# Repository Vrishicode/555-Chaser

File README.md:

# 555-Chaser
Basic description: This is a blinky board/ 555 led chaser which i made for forge in hack club and i changed it and made it so that it looks like a clock.
Why i built it: So i was looking for a project in the guides that was not too difficult so that i could get my hands dirty/ get used to how kicad works and building by first pcb. I just wanted to build this so i would understand how kicad works before moving onto harder/more complex projects and make things that are interesting and make things to build a portfolio.

Whats next: I used this to understand the basics of kicad before moving onto a harder guide/project which is the flight controller and after i will move on to making various controllers for video games like for a racing game, war thunder, etc.

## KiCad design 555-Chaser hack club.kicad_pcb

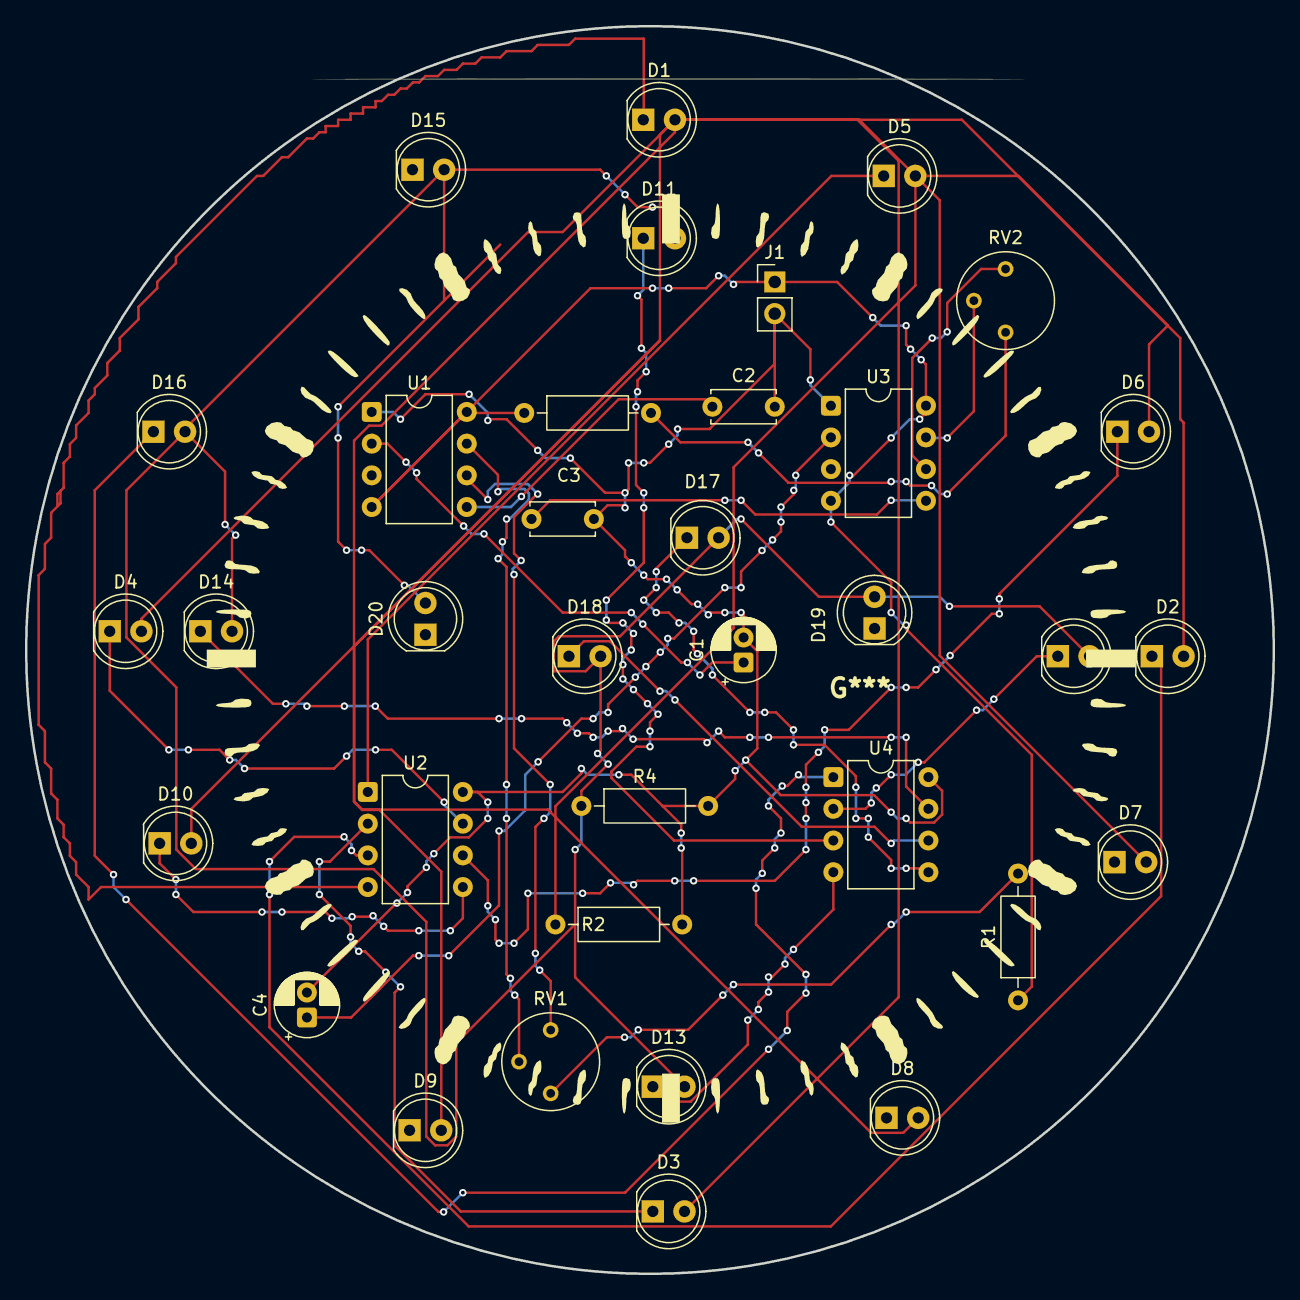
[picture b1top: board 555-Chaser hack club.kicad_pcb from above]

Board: 2 copper layers, 100.0 x 100.0 mm, 35 parts (0 on the bottom side), 28 nets.

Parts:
C1, C4: 1 uF; CP_Radial_D5.0mm_P2.00mm
C2, C3: 0.01 uF; C_Disc_D5.0mm_W2.5mm_P5.00mm
D1, D2, D3, D4, D5, D6, D7, D8, D9, D10, D11, D12, D13, D14, D15, D16, D17, D18, D19, D20: LED; LED_D5.0mm
J1: Conn_01x02_Socket; PinHeader_1x02_P2.54mm_Vertical
R1, R3: 1k; R_Axial_DIN0207_L6.3mm_D2.5mm_P10.16mm_Horizontal
R2, R4: 470; R_Axial_DIN0207_L6.3mm_D2.5mm_P10.16mm_Horizontal
RV1, RV2: 50k; Potentiometer_Bourns_3339P_Vertical
U1, U3: NE555P; DIP-8_W7.62mm
U2, U4: 4017; DIP-8_W7.62mm

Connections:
+5V: J1.1, R1.1, R3.1, U1.4 (~RST), U1.8 (VCC), U3.4 (~RST), U3.8 (VCC)
GND: C1.2, C2.2, C3.2, C4.2, J1.2, R2.2, R4.2, U1.1 (GND), U2.8 (VSS), U3.1 (GND), U4.8 (VSS)
unnamed: D1.2 (A), D2.2 (A), D3.2 (A), D4.2 (A), D5.2 (A), D6.2 (A), D7.2 (A), D8.2 (A), D9.2 (A), D10.2 (A), R2.1
unnamed: D1.1 (K), U2.4 (Q2)
unnamed: D2.1 (K), U2.3 (Q0)
unnamed: D3.1 (K), U2.2 (Q1)
unnamed: D4.1 (K), U2.7 (Q3)
unnamed: D5.1 (K), U2.1 (Q5)
unnamed: D6.1 (K), U2.6 (Q7)
unnamed: D10.1 (K), U2.5 (Q6)
unnamed: D11.2 (A), D12.2 (A), D13.2 (A), D14.2 (A), D15.2 (A), D16.2 (A), D17.2 (A), D18.2 (A), D19.2 (A), D20.2 (A), R4.1
unnamed: D11.1 (K), U4.3 (Q0)
unnamed: D12.1 (K), U4.2 (Q1)
unnamed: D13.1 (K), U4.4 (Q2)
unnamed: D14.1 (K), U4.7 (Q3)
unnamed: D16.1 (K), U4.1 (Q5)
unnamed: D17.1 (K), U4.5 (Q6)
unnamed: D18.1 (K), U4.6 (Q7)
unnamed: R1.2, RV1.1
unnamed: R3.2, RV2.1
unnamed: C2.1, U1.5 (CONT)
unnamed: RV1.2, U1.7 (DISCH)
unnamed: RV1.3, U1.6 (THRES)
unnamed: C1.1, U1.2 (TRIG)
unnamed: C3.1, U3.5 (CONT)
unnamed: RV2.2, U3.7 (DISCH)
unnamed: RV2.3, U3.6 (THRES)
unnamed: C4.1, U3.2 (TRIG)
